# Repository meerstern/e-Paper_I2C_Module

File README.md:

# e-Paper I2C モジュール
The e-Paper I2C Module of Kicad Files for 1.54inch E-Ink raw display panel. 

e-Paper I2Cモジュールは[WAVESHARE製200x200, 1.54inch E-Inkディスプレイ][0]を搭載したモジュールです。<br>
[WAVESHARE製200x200, 1.54inch E-Inkディスプレイ][0]はSPI接続ですが、
配線の容易性を実現するために[SPI I2CプロトコルブリッジIC SC18IS602B][1]を搭載してI2C化しています。<br>
I2C接続のため、SPI接続に比べて描画速度が遅くなりますが、I2C接続で電源線と信号線2本で簡単に接続が可能です。<br>
また、I2CはGroveコネクタを搭載することでラピッドプロトタイピングに対応しています。<br><br>

サンプルプログラムはArduinoとSTM32(SW4STM32)のコードがあります。<br>
[メーカ提供のデモプログラム][2]をSPI I2CプロトコルブリッジICを介して動作するように書き換えています。<br><br>

※注意※<br>
 基板裏面に[V2]マークがある場合は[V2版1.54inch E-Inkディスプレイ][2]のため、V2が付いたサンプルプログラムを使用してください。
V1とV2はハードウェア上の互換性がありますが、プログラム/ファームウェアの互換性はありません。2020年4月以降はV2版が出荷されます。<br>

## e-Paper I2Cモジュール仕様
  * WAVESHARE製200x200, 1.54inch E-Inkディスプレイ搭載
  * 電源3.3V、I2C接続(Groveコネクタ)
  * E-Inkディスプレイの制御ピンはSPI I2CプロトコルブリッジICのGPIOピンに接続されています<br>
  　GPIO0:CS、GPIO1:Busy、GPIO2:DC、GPIO3:Reset
  * 取付穴M3、穴ピッチ44mm x29mm
  
## 販売サイト
  * [スイッチサイエンス][3]

## 告知
  * SC18IS602の後継ICのSC18IS606PWJはGPIOピンが3つに減ったため、本モジュールの代替ICとして使用できないことが分かりました  
  * よって、SC18IS602の生産完了に伴い、本モジュールについてもIC在庫がなくなり次第、販売を終了する予定です  

[0]: https://www.waveshare.com/product/1.54inch-e-paper.htm "*0"
[1]: https://www.nxp.com/products/analog/signal-chain/bridges/ic-bus-to-spi-bridge:SC18IS602B "*1"
[2]: https://www.waveshare.com/wiki/1.54inch_e-Paper_Module "*2"
[3]: https://www.switch-science.com/products/3887

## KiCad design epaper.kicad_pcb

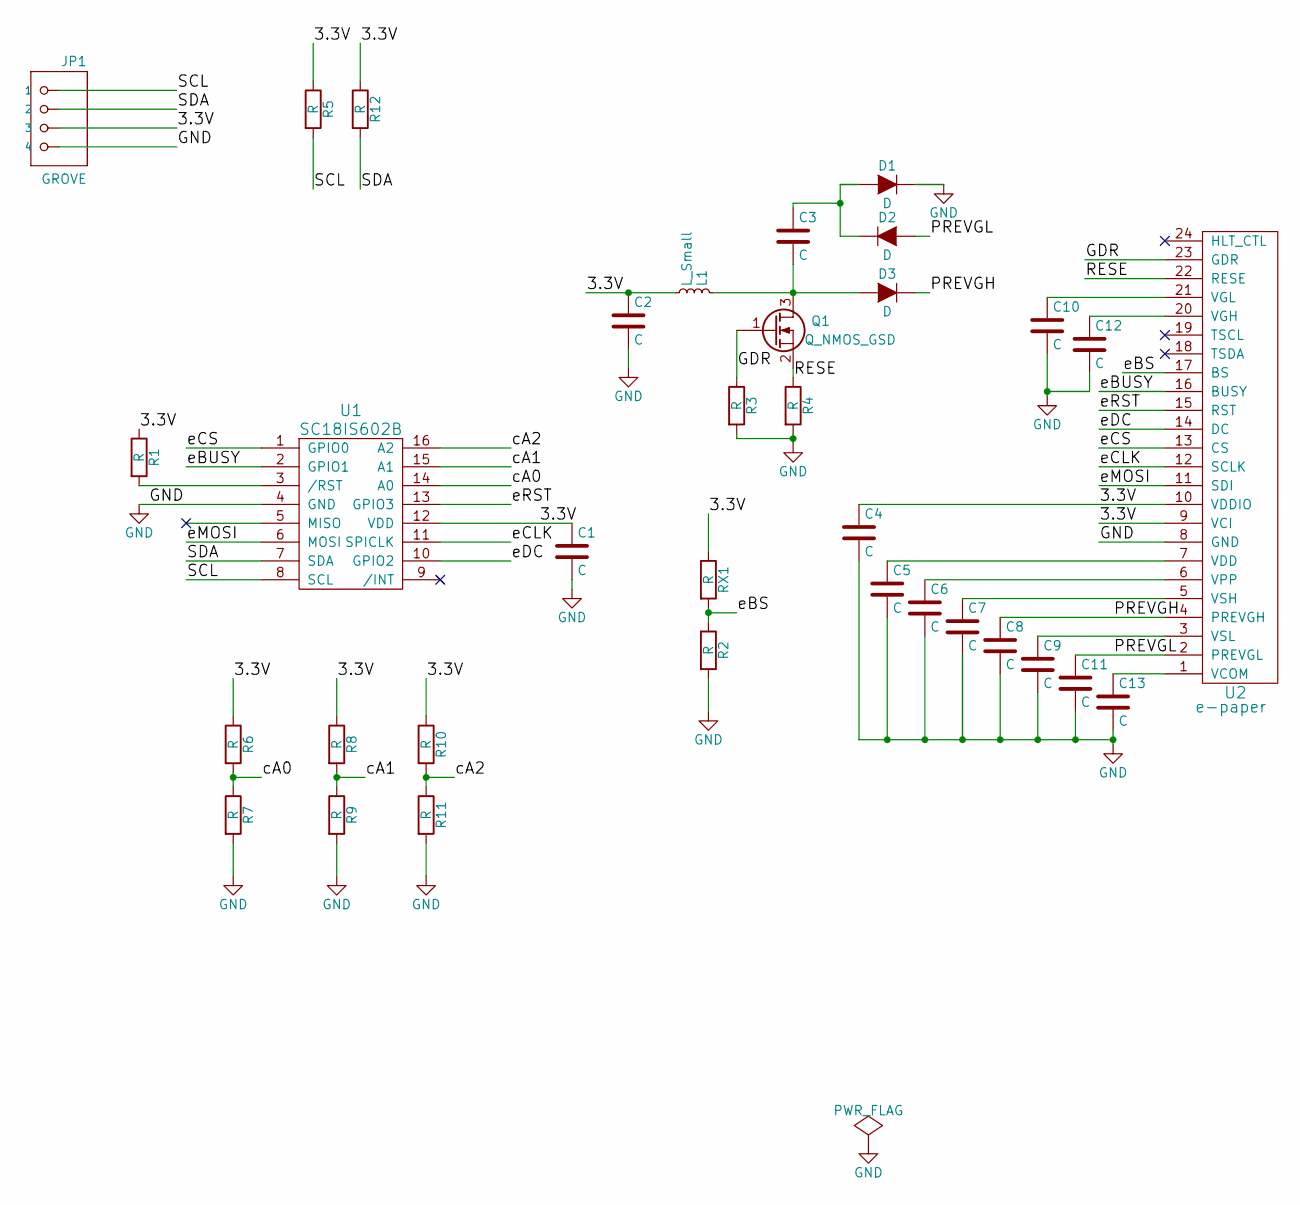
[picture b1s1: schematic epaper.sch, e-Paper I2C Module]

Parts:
C1, C2, C3, C4, C5, C6, C7, C8, C9, C10, C11, C12, C13: C; C-0603
D1, D2, D3: D; SOD-123
JP1: GROVE
L1: L_Small; rcl-L3230M
Q1: Q_NMOS_GSD; SOT23
R1, R2, R3, R4, R5, R6, R7, R8, R9, R10, R11, R12: R; R-0603
RX1: R; R-0603
U1: SC18IS602B; TSSOP-16_4.4x5mm_Pitch0.65mm_without_pad
U2: e-paper; 24pin0.5mm

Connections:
/3.3V: C1.1, C2.1, C4.1, JP1.3, L1.2, R1.1, R5.1, R6.1, R8.1, R10.1, R12.1, RX1.1, U1.12 (VDD), U2.9 (VCI), U2.10 (VDDIO)
/GDR: Q1.1 (G), R3.1, U2.23 (GDR)
/PREVGH: C8.1, D3.K, U2.4 (PREVGH)
/PREVGL: C11.1, D2.A, U2.2 (PREVGL)
/RESE: Q1.2 (S), R4.1, U2.22 (RESE)
/SCL: JP1.1, R5.2, U1.8 (SCL)
/SDA: JP1.2, R12.2, U1.7 (SDA)
/cA0: R6.2, R7.1, U1.14 (A0)
/cA1: R8.2, R9.1, U1.15 (A1)
/cA2: R10.2, R11.1, U1.16 (A2)
/eBS: R2.1, RX1.2, U2.17 (BS)
/eBUSY: U1.2 (GPIO1), U2.16 (BUSY)
/eCLK: U1.11 (SPICLK), U2.12 (SCLK)
/eCS: U1.1 (GPIO0), U2.13 (CS)
/eDC: U1.10 (GPIO2), U2.14 (DC)
/eMOSI: U1.6 (MOSI), U2.11 (SDI)
/eRST: U1.13 (GPIO3), U2.15 (RST)
GND: C1.2, C2.2, C4.2, C5.2, C6.2, C7.2, C8.2, C9.2, C10.2, C11.2, C12.2, C13.2, D1.K, JP1.4, R2.2, R3.2, R4.2, R7.2, R9.2, R11.2, U1.4 (GND), U2.8 (GND)
unnamed: C3.1, D1.A, D2.K
unnamed: C3.2, D3.A, L1.1, Q1.3 (D)
unnamed: C5.1, U2.7 (VDD)
unnamed: C6.1, U2.6 (VPP)
unnamed: C7.1, U2.5 (VSH)
unnamed: C9.1, U2.3 (VSL)
unnamed: C10.1, U2.21 (VGL)
unnamed: C12.1, U2.20 (VGH)
unnamed: C13.1, U2.1 (VCOM)
unnamed: R1.2, U1.3 (/RST)

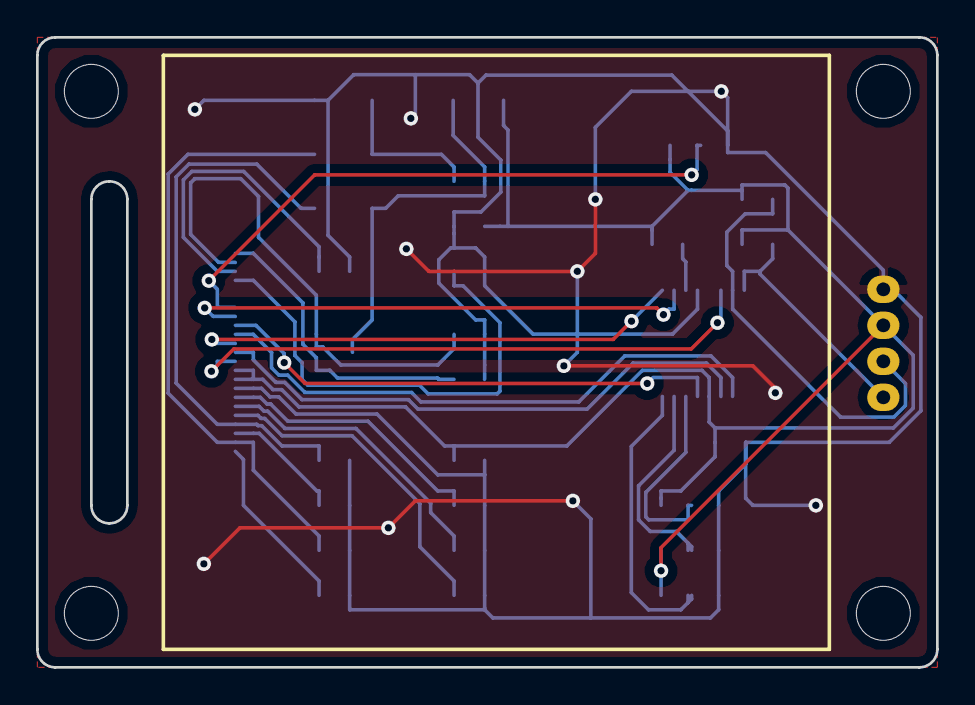
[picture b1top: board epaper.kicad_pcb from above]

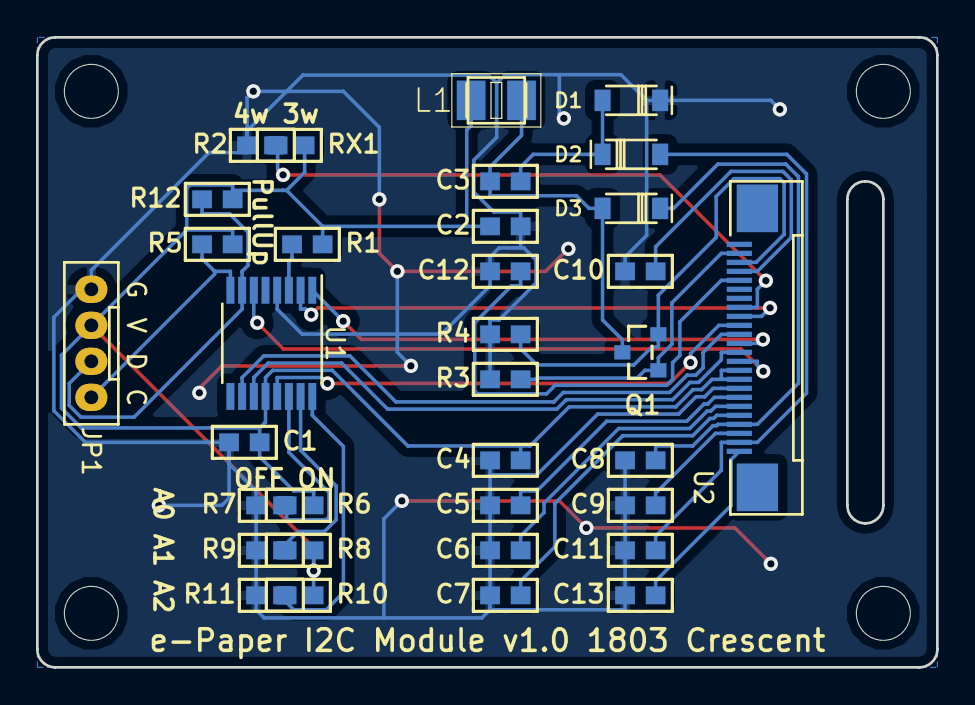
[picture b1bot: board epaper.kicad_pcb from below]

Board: 2 copper layers, 50.0 x 35.0 mm, 38 parts (34 on the bottom side), 28 nets.

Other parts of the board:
REF1, REF2, REF3, REF4: MountingHole_3mm

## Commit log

2018-05-19 Init
2018-05-19 Fix the position of the HFL Connector
2018-05-19 Add sample code
2018-05-30 Add Photo
2019-02-28 Update ino file for initizalition fail.
    Some MPU such as Arduino UNO cause initizalition fail.
    To avoid them, enable clear memory.
2019-11-16 Add sample code for V2
2019-11-23 Update for E-ink V2
2022-12-06 Add shop link
